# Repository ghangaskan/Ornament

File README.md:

# Ornament
Christmas ornament LED chaser from NE555P and CD4017BE

If this works when it comes back from fab, it should be a LED chaser down both sides of the tree.

I didn't give it a power source, so I should do that. I was figuring I would just power it directly from a 5v transformer to one of the shared GND and VCC pins. I may get back to it soon to resolve.
Or...
I may also be reworking another ornament using a CH32v003 instead of the more expensive 555.

The combination of SMD and through hole parts correlates to stuff I have laying around.

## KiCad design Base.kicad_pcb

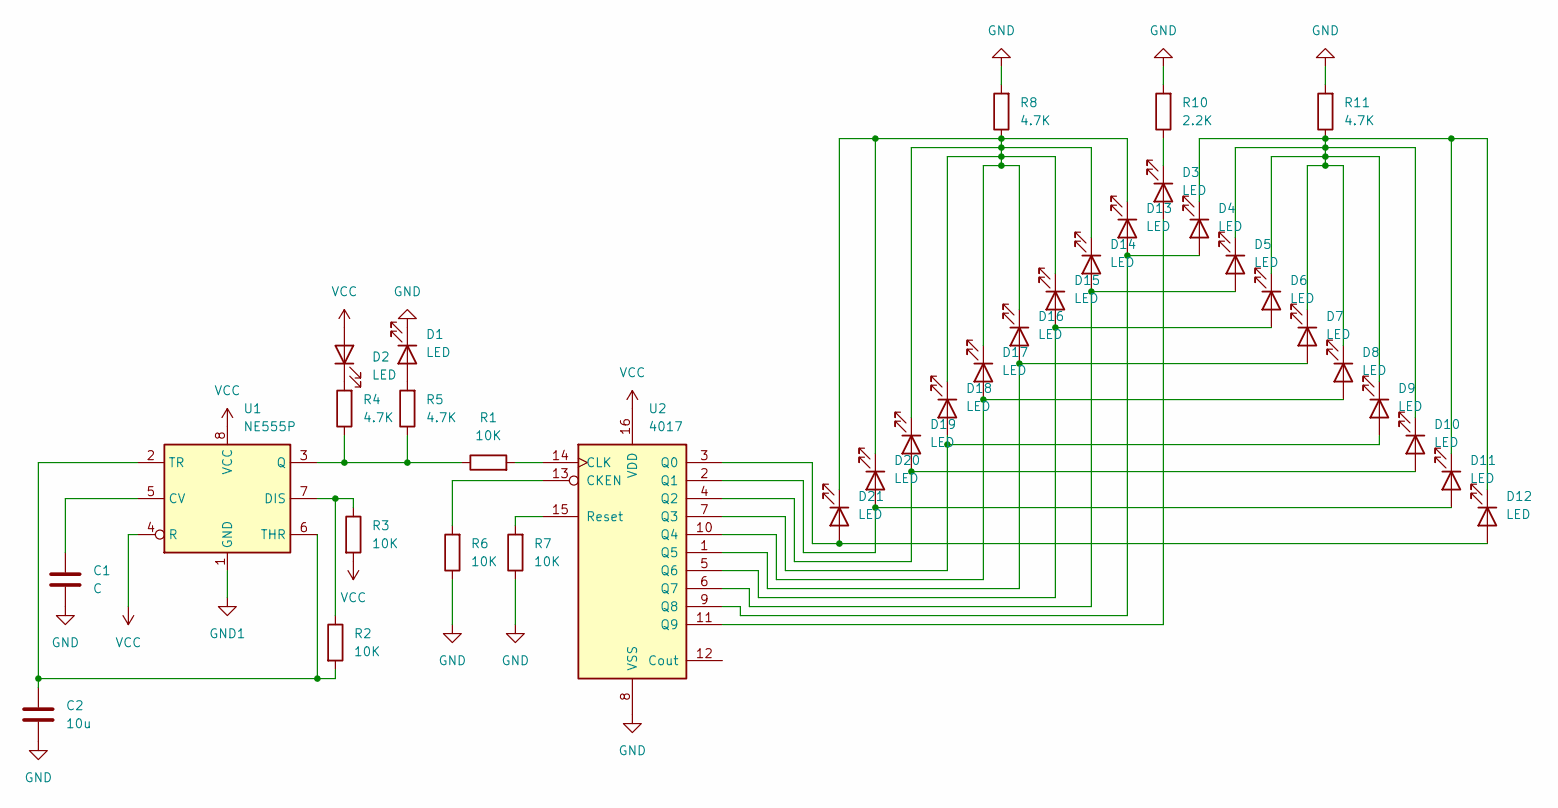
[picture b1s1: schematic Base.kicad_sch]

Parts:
C1: C; C_Disc_D5.0mm_W2.5mm_P5.00mm
C2: 10u; C_Disc_D5.0mm_W2.5mm_P5.00mm
D1, D2: LED; LED_D4.0mm
D3, D4, D5, D6, D7, D8, D9, D10, D11, D12, D13, D14, D15, D16, D17, D18, D19, D20, D21: LED; LED_2512_6332Metric_Pad1.52x3.35mm_HandSolder
R1, R2, R3, R6, R7: 10K; R_Axial_DIN0204_L3.6mm_D1.6mm_P5.08mm_Horizontal
R4, R5, R8, R11: 4.7K; R_Axial_DIN0204_L3.6mm_D1.6mm_P5.08mm_Horizontal
R10: 2.2K; R_Axial_DIN0204_L3.6mm_D1.6mm_P5.08mm_Horizontal
U1: NE555P; DIP-8_W7.62mm
U2: 4017; DIP-16_W7.62mm

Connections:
GND: C1.2, C2.2, D1.1 (K), R6.1, R7.1, R8.2, R10.2, R11.2, U2.8 (VSS)
GND1: U1.1 (GND)
unnamed: D1.2 (A), R5.2
unnamed: D2.1 (K), R4.2
unnamed: D3.2 (A), U2.11 (Q9)
unnamed: D3.1 (K), R10.1
unnamed: D10.2 (A), D19.2 (A), U2.4 (Q2)
unnamed: D4.1 (K), D5.1 (K), D6.1 (K), D7.1 (K), D8.1 (K), D9.1 (K), D10.1 (K), D11.1 (K), D12.1 (K), R11.1
unnamed: D11.2 (A), D20.2 (A), U2.2 (Q1)
unnamed: D12.2 (A), D21.2 (A), U2.3 (Q0)
unnamed: D4.2 (A), D13.2 (A), U2.9 (Q8)
unnamed: D13.1 (K), D14.1 (K), D15.1 (K), D16.1 (K), D17.1 (K), D18.1 (K), D19.1 (K), D20.1 (K), D21.1 (K), R8.1
unnamed: D5.2 (A), D14.2 (A), U2.6 (Q7)
unnamed: D6.2 (A), D15.2 (A), U2.5 (Q6)
unnamed: D7.2 (A), D16.2 (A), U2.1 (Q5)
unnamed: D8.2 (A), D17.2 (A), U2.10 (Q4)
unnamed: D9.2 (A), D18.2 (A), U2.7 (Q3)
unnamed: C1.1, U1.5 (CV)
unnamed: R2.1, R3.1, U1.7 (DIS)
unnamed: R1.1, R4.1, R5.1, U1.3 (Q)
unnamed: C2.1, R2.2, U1.2 (TR), U1.6 (THR)
unnamed: R6.2, U2.13 (CKEN)
unnamed: R1.2, U2.14 (CLK)
unnamed: R7.2, U2.15 (Reset)
VCC: D2.2 (A), R3.2, U1.4 (R), U1.8 (VCC), U2.16 (VDD)

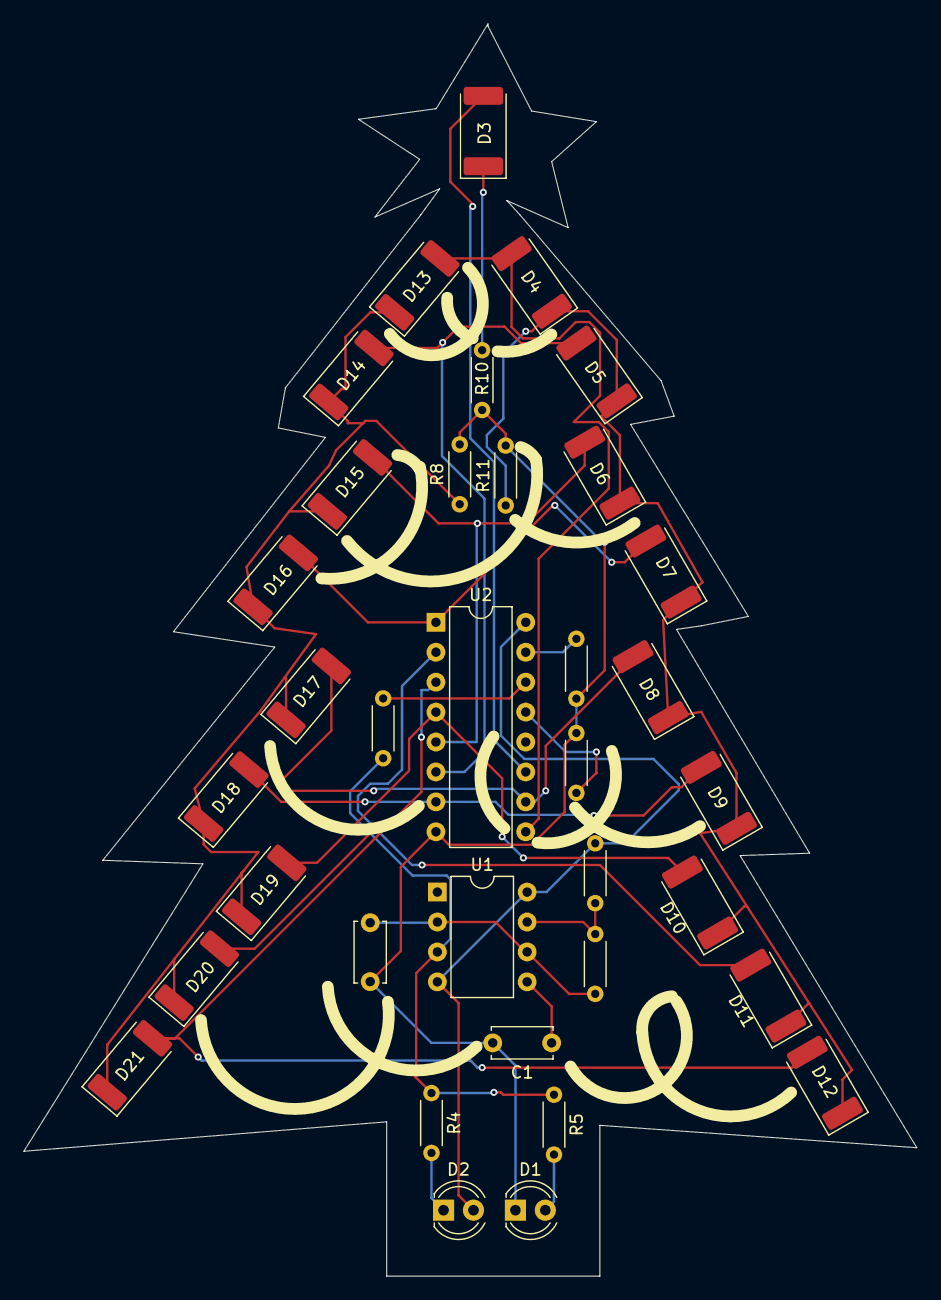
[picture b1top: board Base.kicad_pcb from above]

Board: 2 copper layers, 75.8 x 106.3 mm, 35 parts (0 on the bottom side), 24 nets.
